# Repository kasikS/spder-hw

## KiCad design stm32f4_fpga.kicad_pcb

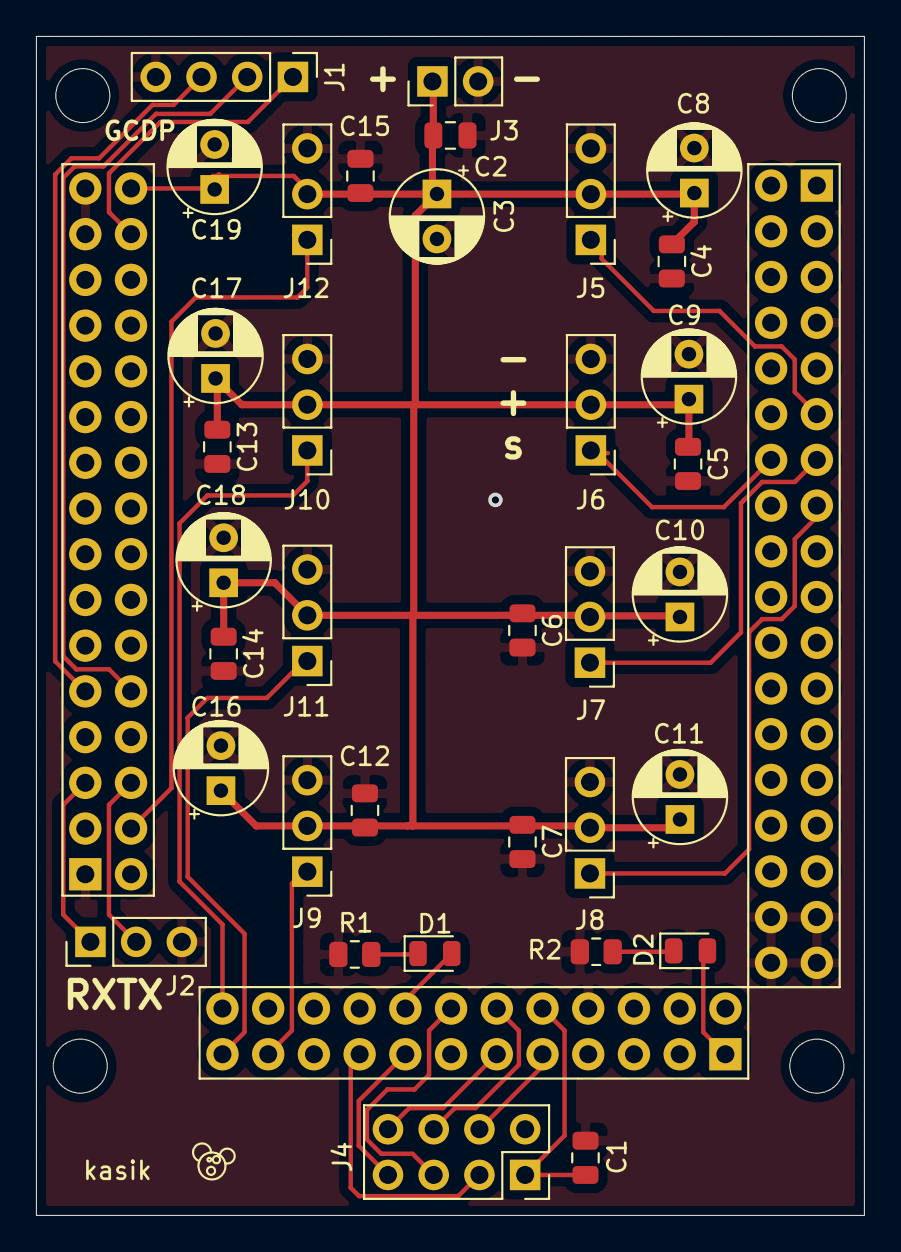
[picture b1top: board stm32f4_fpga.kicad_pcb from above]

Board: 2 copper layers, 46.0 x 65.5 mm, 36 parts (0 on the bottom side), 26 nets.

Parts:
C1, C2, C4, C5, C6, C7, C12, C13, C14, C15: 100n; C_0805_2012Metric
C3, C8, C9, C10, C11, C16, C17, C18, C19: 47u/16V; CP_Radial_D5.0mm_P2.50mm
D1, D2: LED; LED_0805_2012Metric
J1: SWD; PinHeader_1x04_P2.54mm_Vertical
J2: Serial; PinHeader_1x03_P2.54mm_Vertical
J3: Power; PinHeader_1x02_P2.54mm_Vertical
J4: nRF24L01; PinSocket_2x04_P2.54mm_Vertical
J5, J6, J7, J8, J9, J10, J11, J12: Servo; PinHeader_1x03_P2.54mm_Vertical
R1, R2: 120; R_0805_2012Metric
U1: DIYMORE-F407VG; DIYMORE-407VG-PINTOP

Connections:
+3V3: C1.1, J4.1, U1.c10
/LED1: D1.2, U1.c16
/LED2: D2.2, U1.c1
/NRF_CE: J4.4, U1.c9
/NRF_CSN: J4.3, U1.c17
/NRF_IRQ: J4.7, U1.c15
/NRF_MISO: J4.8, U1.c11
/NRF_MOSI: J4.5, U1.c14
/NRF_SCK: J4.6, U1.c12
/SWCLK: J1.3, U1.a9
/SWDIO: J1.2, U1.a10
/TIM2_CH1: J5.1, U1.b11
/TIM2_CH2: J6.1, U1.b14
/TIM2_CH3: J7.1, U1.b13
/TIM2_CH4: J8.1, U1.b15
/TIM3_CH1: J9.1, U1.c21
/TIM3_CH2: J10.1, U1.c24
/TIM3_CH3: J11.1, U1.c23
/TIM3_CH4: J12.1, U1.a4
/UART_RX: J2.1, U1.a5
/UART_TX: J2.2, U1.a6
GND: C1.2, C2.2, C3.2, C4.2, C5.2, C6.2, C7.2, C8.2, C9.2, C10.2, C11.2, C12.2, C13.2, C14.2, C15.2, C16.2, C17.2, C18.2, C19.2, J1.4, J2.3, J3.2, J4.2, J5.3, J6.3, J7.3, J8.3, J9.3, J10.3, J11.3, J12.3, R1.2, R2.2, U1.a1, U1.a29, U1.a31, U1.b7, U1.b33, U1.b34, U1.b35, U1.b36, U1.c8
unnamed: D1.1, R1.1
unnamed: D2.1, R2.1
unnamed: J1.1, U1.a30
VCC: C2.1, C3.1, C4.1, C5.1, C6.1, C7.1, C8.1, C9.1, C10.1, C11.1, C12.1, C13.1, C14.1, C15.1, C16.1, C17.1, C18.1, C19.1, J3.1, J5.2, J6.2, J7.2, J8.2, J9.2, J10.2, J11.2, J12.2, U1.a32
